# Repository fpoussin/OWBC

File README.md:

View this project on [CADLAB.io](https://cadlab.io/node/809). 

# OWBC
Open source/hardware LSU 4.9 wideband controller

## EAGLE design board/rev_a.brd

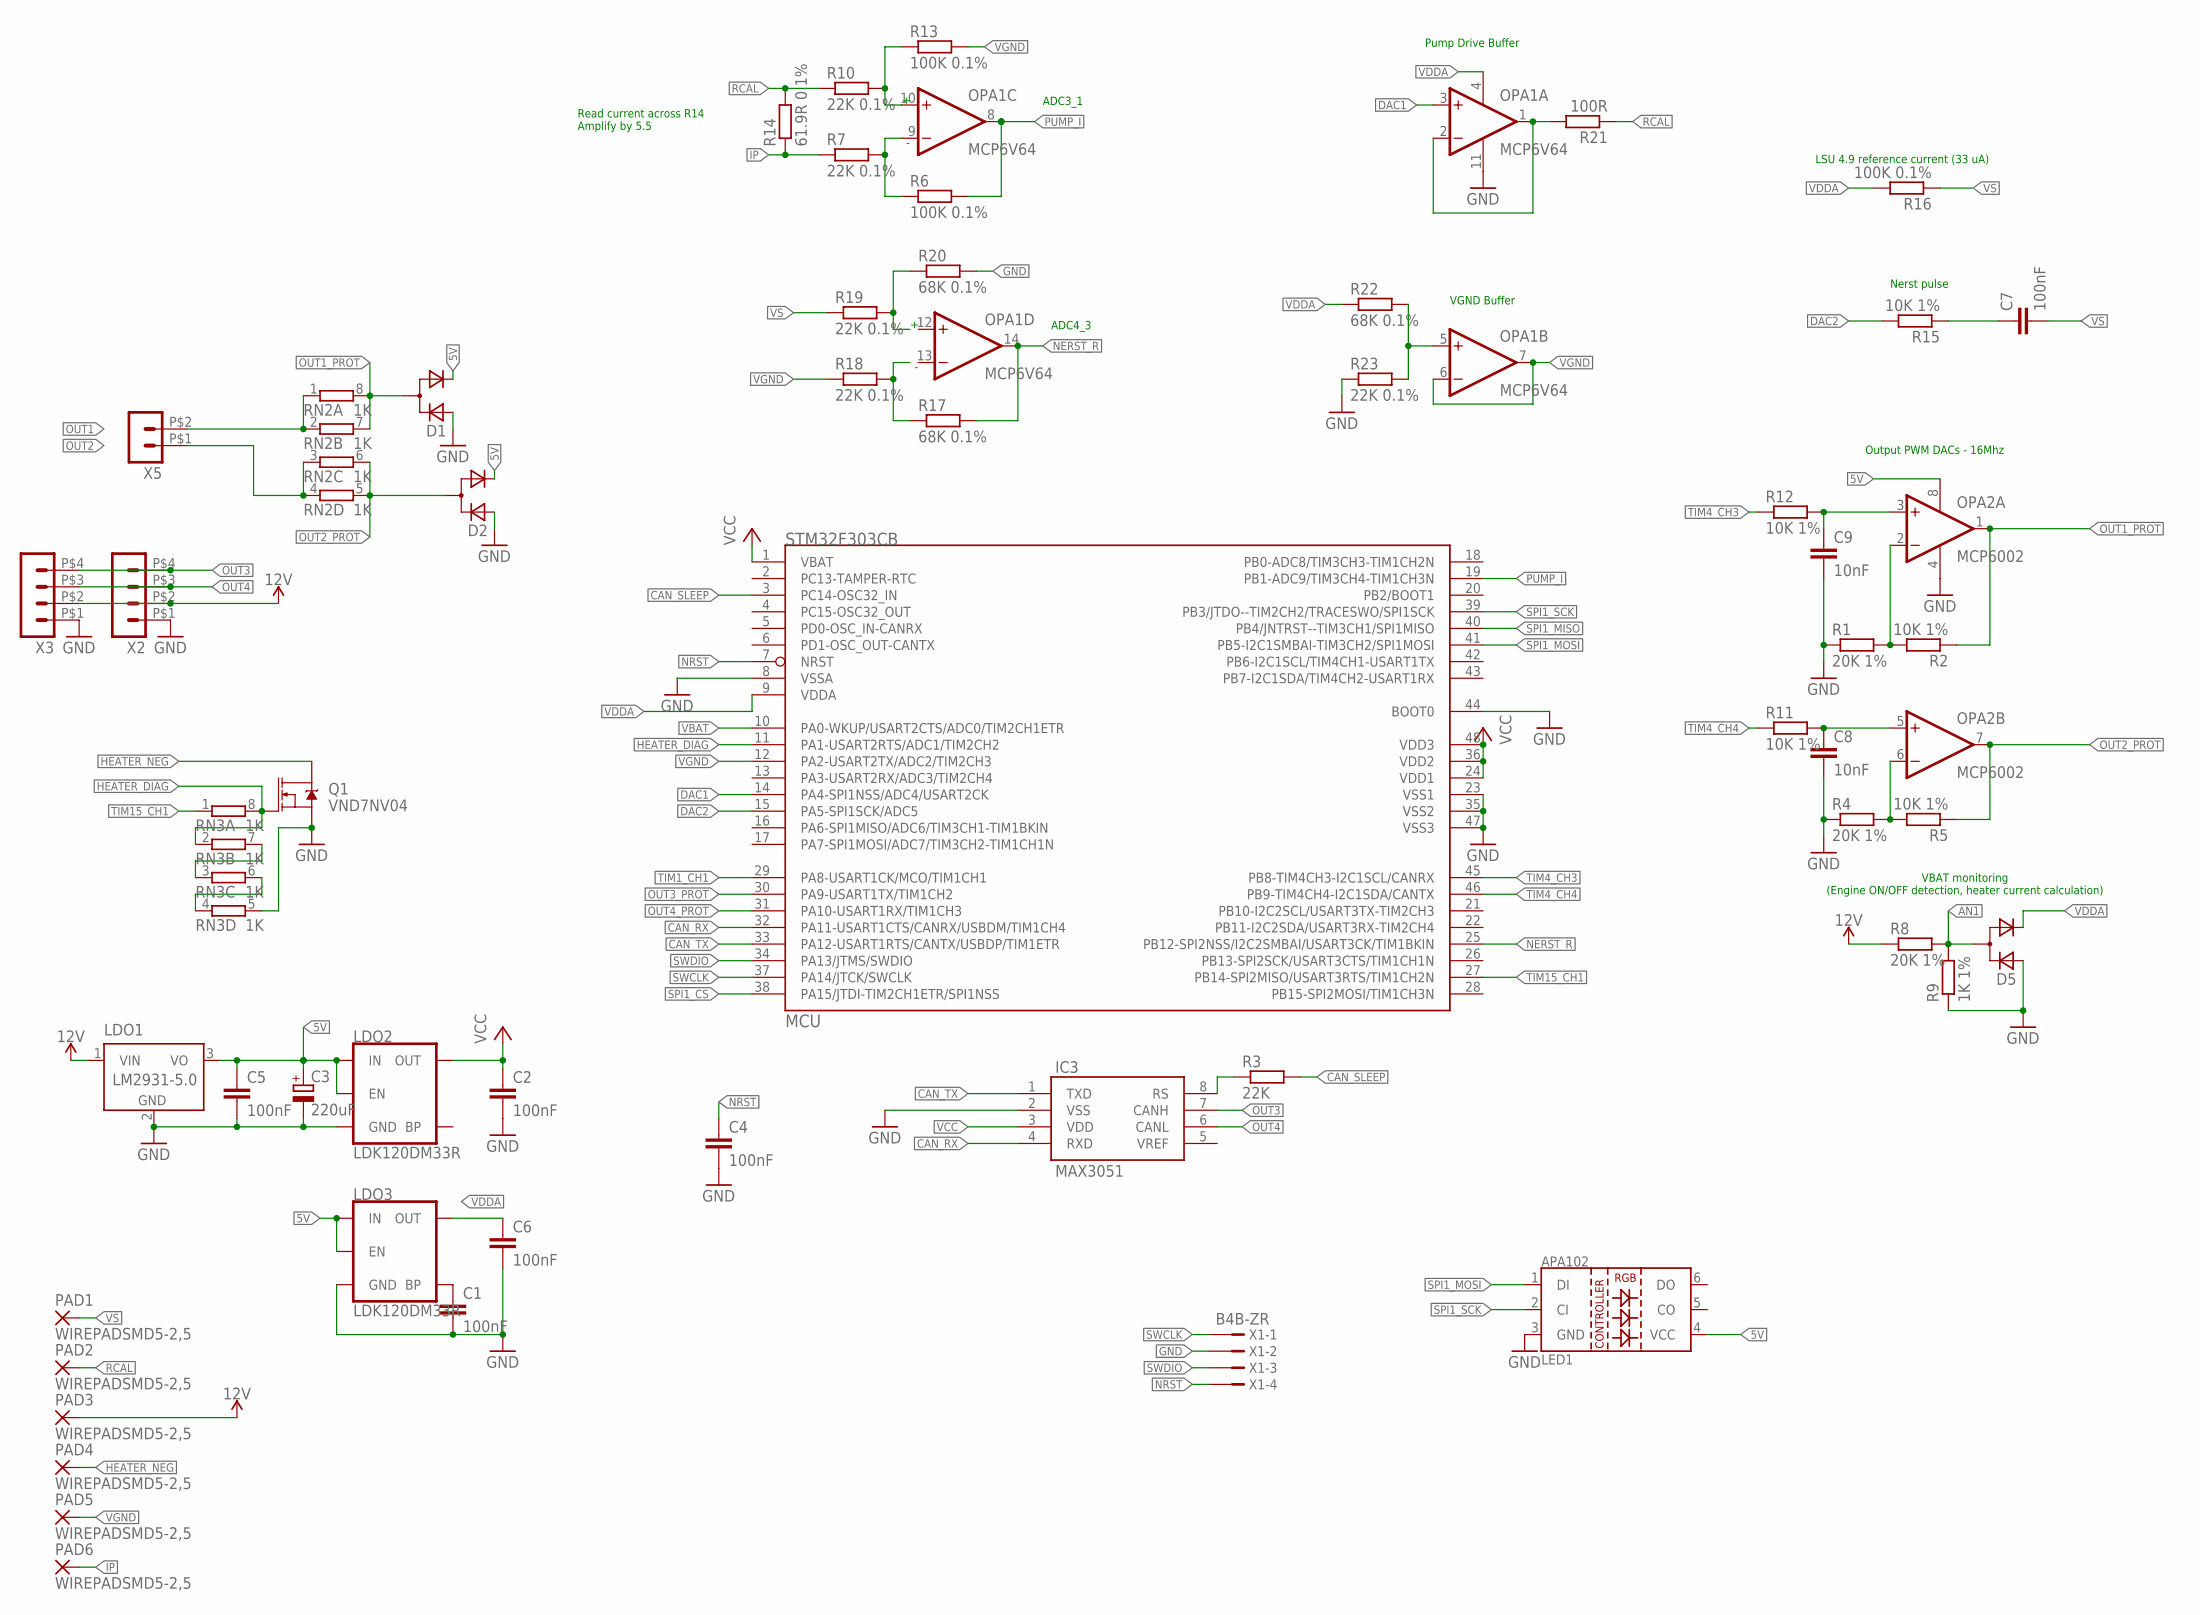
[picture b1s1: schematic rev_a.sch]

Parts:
C1, C2, C4, C5, C6, C7: 100nF; C0603
C3: 220uF; E2,5-5
C8, C9: 10nF; C0603
D1, D2, D5: D_ACACSOT323; SOT323
IC3: MAX3051; SO08
LDO1: LM2931-5.0; TO252
LDO2, LDO3: LDK120DM33R; SOT23-5
LED1: LED-APA102
MCU: STM32F303CB; LQFP48
OPA1: MCP6V64; TSSOP14
OPA2: MCP6002; TSSOP8
PAD1, PAD2, PAD3, PAD4, PAD5, PAD6: WIREPADSMD5-2,5; 5-2,5
Q1: VND7NV04; DPAK
R1, R4, R8: 20K 1%; R0603
R2, R5, R11, R12, R15: 10K 1%; R0603
R3: 22K; R0603
R6, R13, R16: 100K 0.1%; R0603
R7, R10, R18, R19, R23: 22K 0.1%; R0603
R9: 1K 1%; R0603
R14: 61.9R 0.1%; R0603
R17, R20, R22: 68K 0.1%; R0603
R21: 100R; R0603
RN2, RN3: 1K; 0603-ARC
X1: B4B-ZR
X2, X3: HEADER_POS4_43045-0401; 43045-0400
X5: HEADER_POS2_43045-0200; 43045-0200

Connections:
5V: C3.+, C5.1, D1.2 (C), D2.2 (C), LDO1.3 (VO), LDO2.1 (IN), LDO2.3 (EN), LDO3.1 (IN), LDO3.3 (EN), LED1.4 (VCC), OPA2.8 (V+)
12V: LDO1.1 (VIN), PAD3.1, R8.1, X2.P$2 (2), X3.P$2 (2)
AN1: D5.1 (CA), R8.2, R9.2
CAN_RX: IC3.4 (RXD), MCU.32 (PA11-USART1CTS/CANRX/USBDM/TIM1CH4)
CAN_SLEEP: MCU.3 (PC14-OSC32_IN), R3.2
CAN_TX: IC3.1 (TXD), MCU.33 (PA12-USART1RTS/CANTX/USBDP/TIM1ETR)
DAC1: MCU.14 (PA4-SPI1NSS/ADC4/USART2CK), OPA1.3 (+IN)
DAC2: MCU.15 (PA5-SPI1SCK/ADC5), R15.2
GND: C1.2, C2.2, C3.-, C4.2, C5.2, C6.2, C8.2, C9.2, D1.3 (A), D2.3 (A), D5.3 (A), IC3.2 (VSS), LDO1.2 (GND), LDO2.2 (GND), LDO3.2 (GND), LED1.3 (GND), MCU.23 (VSS1), MCU.35 (VSS2), MCU.44 (BOOT0), MCU.47 (VSS3), OPA1.11 (V-), OPA2.4 (V-), Q1.3 (S), R1.1, R4.1, R9.1, R20.2, R23.1, RN3.5 (2), X1.2, X2.P$1 (1), X3.P$1 (1)
HEATER_DIAG: MCU.11 (PA1-USART2RTS/ADC1/TIM2CH2), Q1.1 (G), RN3.2 (1), RN3.8 (2)
HEATER_NEG: PAD4.1, Q1.4 (D)
IP: PAD6.1, R7.1, R14.1
unnamed: RN3.3 (1), RN3.7 (2)
unnamed: C8.1, OPA2.5 (+IN), R11.2
unnamed: OPA2.2 (-IN), R1.2, R2.2
unnamed: OPA2.6 (-IN), R4.2, R5.2
unnamed: RN3.4 (1), RN3.6 (2)
unnamed: IC3.8 (RS), R3.1
unnamed: OPA1.5 (+IN), R22.2, R23.2
unnamed: C1.1, LDO3.4 (BP)
unnamed: C7.1, R15.1
unnamed: C9.1, OPA2.3 (+IN), R12.2
unnamed: OPA1.1 (OUT), OPA1.2 (-IN), R21.2
NERST_R: MCU.25 (PB12-SPI2NSS/I2C2SMBAI/USART3CK/TIM1BKIN), OPA1.14 (OUT), R17.2
NRST: C4.1, MCU.7 (NRST), X1.4
OPA3_IN+: OPA1.10 (+IN), R10.2, R13.1
OPA3_IN-: OPA1.9 (-IN), R6.1, R7.2
OPA4_IN+: R19.2, R20.1
OPA4_IN-: R17.1, R18.2
OUT1: RN2.1, RN2.2 (1), X5.P$2 (2)
OUT1_PROT: D1.1 (CA), OPA2.1 (OUT), R2.1, RN2.7 (2), RN2.8 (2)
OUT2: RN2.3 (1), RN2.4 (1), X5.P$1 (1)
OUT2_PROT: D2.1 (CA), OPA2.7 (OUT), R5.1, RN2.5 (2), RN2.6 (2)
OUT3: IC3.7 (CANH), X2.P$4 (4), X3.P$4 (4)
OUT3_PROT: MCU.30 (PA9-USART1TX/TIM1CH2)
OUT4: IC3.6 (CANL), X2.P$3 (3), X3.P$3 (3)
OUT4_PROT: MCU.31 (PA10-USART1RX/TIM1CH3)
PUMP_I: MCU.19 (PB1-ADC9/TIM3CH4-TIM1CH3N), OPA1.8 (OUT), R6.2
RCAL: PAD2.1, R10.1, R14.2, R21.1
SPI1_CS: MCU.38 (PA15/JTDI-TIM2CH1ETR/SPI1NSS)
SPI1_MISO: MCU.40 (PB4/JNTRST--TIM3CH1/SPI1MISO)
SPI1_MOSI: LED1.1 (DI), MCU.41 (PB5-I2C1SMBAI-TIM3CH2/SPI1MOSI)
SPI1_SCK: LED1.2 (CI), MCU.39 (PB3/JTDO--TIM2CH2/TRACESWO/SPI1SCK)
SWCLK: MCU.37 (PA14/JTCK/SWCLK), X1.1
SWDIO: MCU.34 (PA13/JTMS/SWDIO), X1.3
TIM1_CH1: MCU.29 (PA8-USART1CK/MCO/TIM1CH1)
TIM4_CH3: MCU.45 (PB8-TIM4CH3-I2C1SCL/CANRX), R12.1
TIM4_CH4: MCU.46 (PB9-TIM4CH4-I2C1SDA/CANTX), R11.1
TIM15_CH1: MCU.27 (PB14-SPI2MISO/USART3RTS/TIM1CH2N), RN3.1
VBAT: MCU.1 (VBAT), MCU.10 (PA0-WKUP/USART2CTS/ADC0/TIM2CH1ETR)
VCC: C2.1, IC3.3 (VDD), LDO2.5 (OUT), MCU.24 (VDD1), MCU.36 (VDD2), MCU.48 (VDD3)
VDDA: C6.1, D5.2 (C), LDO3.5 (OUT), MCU.9 (VDDA), OPA1.4 (V+), R16.2
VGND: MCU.12 (PA2-USART2TX/ADC2/TIM2CH3), OPA1.6 (-IN), OPA1.7 (OUT), PAD5.1, R13.2, R18.1
VS: C7.2, PAD1.1, R16.1, R19.1
VSSA: MCU.8 (VSSA)

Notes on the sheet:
VBAT monitoring (Engine ON/OFF detection, heater current calculation)
VGND Buffer
Pump Drive Buffer
Output PWM DACs - 16Mhz
ADC3_1
ADC4_3
Nerst pulse
Read current across R14 Amplify by 5.5
LSU 4.9 reference current (33 uA)

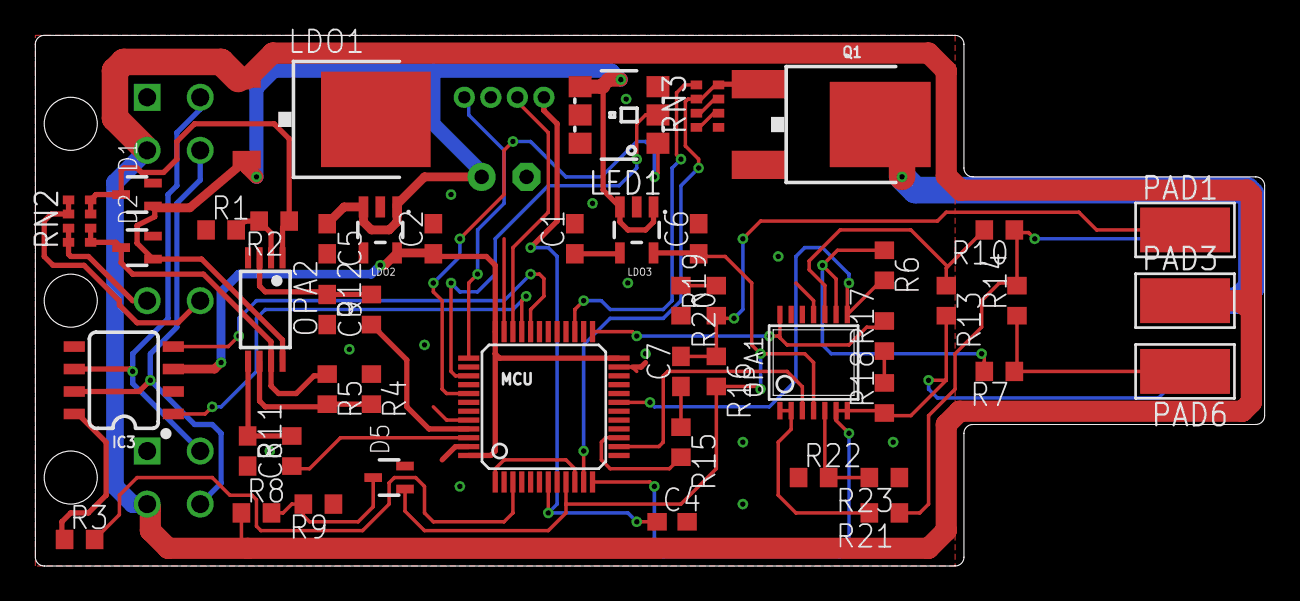
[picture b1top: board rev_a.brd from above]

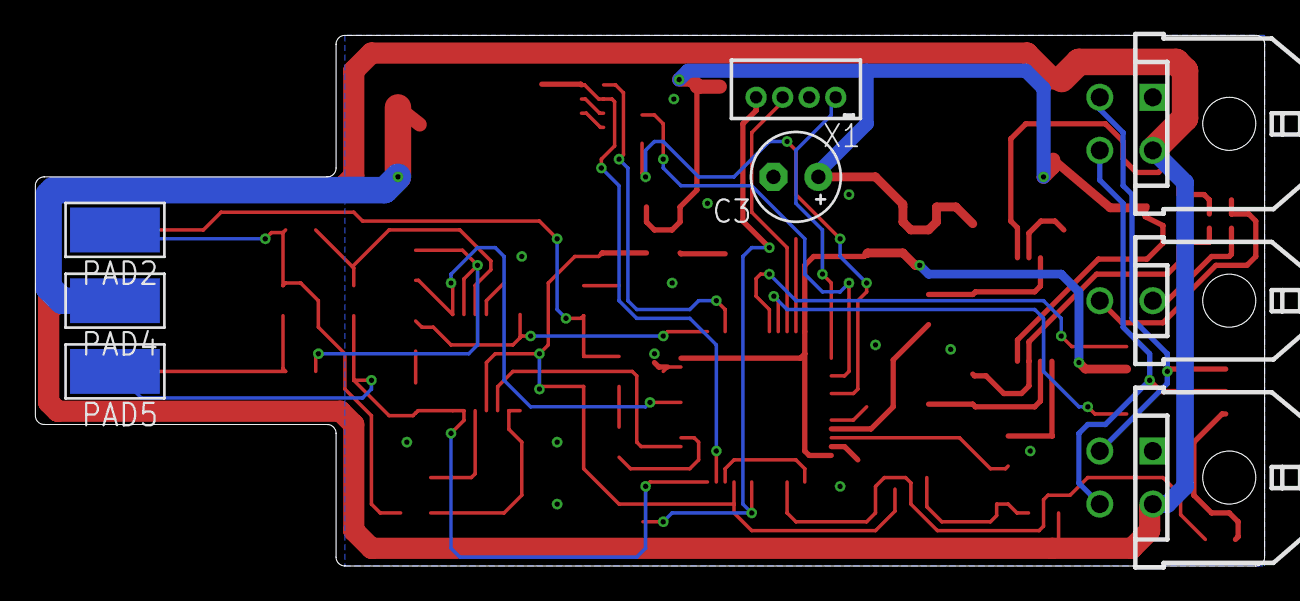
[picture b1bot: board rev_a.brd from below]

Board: 2 copper layers, 69.5 x 30.0 mm, 56 parts (8 on the bottom side), 49 nets.

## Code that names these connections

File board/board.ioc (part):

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Mcu.Name=STM32F303C(B-C)Tx
Mcu.Package=LQFP48
Mcu.UserName=STM32F303CBTx
PA0.Mode=IN1-Single-Ended
PA0.Signal=ADC1_IN1
PA10.GPIOParameters=GPIO_Speed
PA10.GPIO_Speed=GPIO_SPEED_FREQ_MEDIUM
PA10.Mode=Asynchronous
PA10.Signal=USART1_RX
PA11.Mode=Master
PA11.Signal=CAN_RX
PA12.Mode=Master
PA12.Signal=CAN_TX
PA13.Mode=Serial_Wire
PA13.Signal=SYS_JTMS-SWDIO
PA14.Mode=Serial_Wire
PA14.Signal=SYS_JTCK-SWCLK
PA15.Mode=NSS_Signal_Hard_Output
PA15.Signal=SPI1_NSS
PA2.Mode=IN3-Single-Ended
PA2.Signal=ADC1_IN3
PA4.Signal=COMP_DAC1_group
PA5.Signal=COMP_DAC2_group
PA8.Signal=S_TIM1_CH1
PA9.GPIOParameters=GPIO_Speed
PA9.GPIO_Speed=GPIO_SPEED_FREQ_MEDIUM
PA9.Mode=Asynchronous
PA9.Signal=USART1_TX
PB1.Mode=IN1-Single-Ended
PB1.Signal=ADC3_IN1
PB12.Mode=IN3-Single-Ended
PB12.Signal=ADC4_IN3
PB14.GPIOParameters=GPIO_Label
PB14.GPIO_Label=HEATER_PWM
PB14.Signal=S_TIM15_CH1
PB3.Mode=Full_Duplex_Master
PB3.Signal=SPI1_SCK
PB4.Mode=Full_Duplex_Master
PB4.Signal=SPI1_MISO
PB5.Mode=Full_Duplex_Master
PB5.Signal=SPI1_MOSI
PB8.Signal=S_TIM4_CH3
PB9.Signal=S_TIM4_CH4
PC13.GPIOParameters=GPIO_PuPd,GPIO_Label
PC13.GPIO_Label=BUTTON1
PC13.GPIO_PuPd=GPIO_PULLUP
PC13.Signal=GPIO_Input
PC14-OSC32_IN.GPIOParameters=GPIO_Label,GPIO_ModeDefaultOutputPP
PC14-OSC32_IN.GPIO_Label=CAN_RS
PC14-OSC32_IN.GPIO_ModeDefaultOutputPP=GPIO_MODE_OUTPUT_OD
PC14-OSC32_IN.Signal=GPIO_Output
RCC.HSEPLLFreq_Value=8000000
RCC.HSE_VALUE=8000000
RCC.SYSCLKFreq_VALUE=8000000

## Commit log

2017-05-17 [code] Adding empty projects
2017-05-18 [board] Updated PCB and IOC files
2017-05-18 [code] Updating I/O and config.
2017-05-18 [code] minor changes
2017-05-18 [board] Cleaning up
2017-05-19 [code] Updating gpio
2017-05-20 [board] Testing a few configurations
2017-05-21 [board] Working on schema
2017-05-22 [board] Adding a few analog circuits
2017-05-22 [board] Replacing diodes with smaller packages
2017-05-22 [code] Updating storage code
2017-05-23 [board] Working on analog
2017-05-23 [code] Minor fixes (storage)
2017-05-23 [code] Adding ugfx
2017-10-14 Routed PCB
2018-03-30 Backlink to CADLAB.io has been added.

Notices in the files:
parts and their libraries:
SparkFun-DiscreteSemi: Licensing: Creative Commons ShareAlike 4.0 International - https://creativecommons.org/licenses/by-sa/4.0
